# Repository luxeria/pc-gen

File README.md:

pc-gen
======

Signal generator using a pc audio output

The idea for this project is based on Debraj's pc based signal generator. 
(https://sites.google.com/site/hobbydebraj/home/pc-based-signal-generator)

The signal generator can be powered by a USB connection. 
Additionally the offset can be set up with the second output channel.

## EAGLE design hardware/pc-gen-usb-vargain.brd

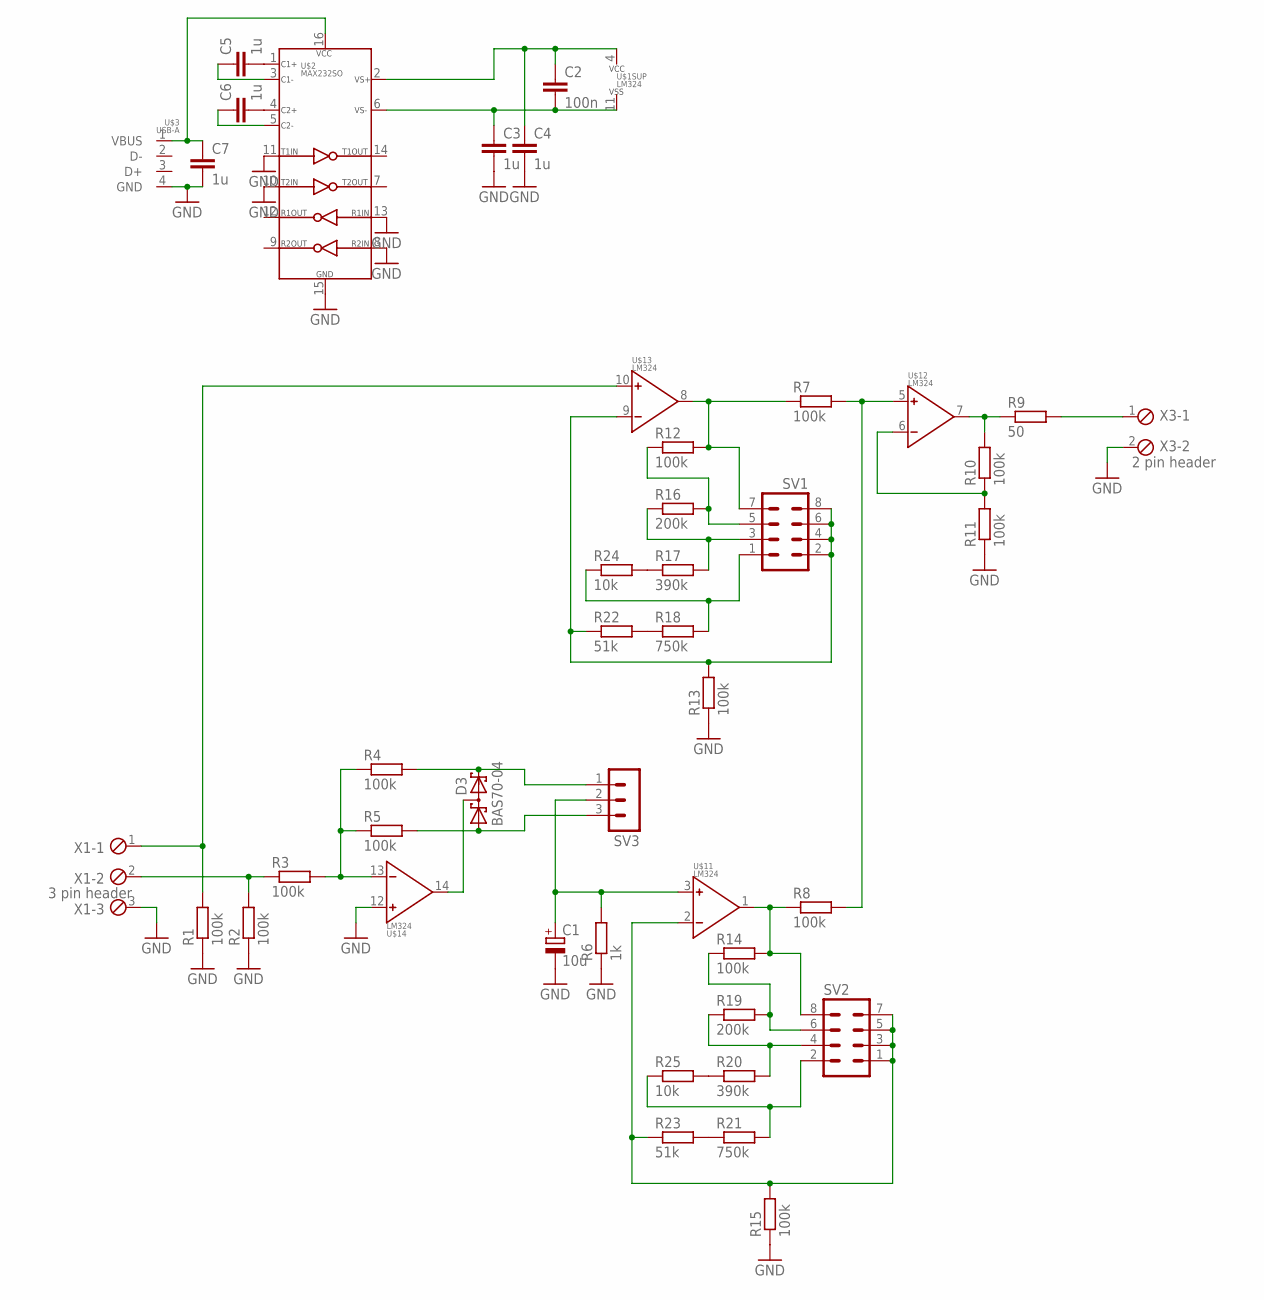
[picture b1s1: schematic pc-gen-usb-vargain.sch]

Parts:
C1: 10u; E2,5-7
C2: 100n; C1206
C3, C4, C5, C6, C7: 1u; C1206
D3: BAS70-04; SOT23
R1, R2, R3, R4, R5, R7, R8, R10, R11, R12, R13, R14, R15: 100k; R1206
R6: 1k; R1206
R9: 50; R1206
R16, R19: 200k; R1206
R17, R20: 390k; R1206
R18, R21: 750k; R1206
R22, R23: 51k; R1206
R24, R25: 10k; R1206
SV1, SV2: MA04-2
SV3: MA03-1
U$1: LM324; SO14
U$2: MAX232SO; SO16
U$3: USB-A
X1: 3 pin header; 3POL254
X3: 2 pin header; 2POL254

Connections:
GND: C1.-, C3.2, C4.2, C7.2, R1.1, R2.1, R6.1, R11.1, R13.1, R15.1, U$1.12 (POS), U$2.8 (R2IN), U$2.10 (T2IN), U$2.11 (T1IN), U$2.13 (R1IN), U$2.15 (GND), U$3.4 (GND), X1.3, X3.2
unnamed: C2.2, C3.1, U$1.11 (VSS), U$2.6 (VS-)
unnamed: C2.1, C4.1, U$1.4 (VCC), U$2.2 (VS+)
unnamed: R2.2, R3.1, X1.2
unnamed: R1.2, U$1.10 (POS), X1.1
unnamed: R16.1, R17.2, SV1.3
unnamed: R3.2, R4.1, R5.1, U$1.13 (NEG)
unnamed: D3.1 (A1), R5.2, SV3.3
unnamed: R7.1, R12.2, SV1.7, U$1.8 (OUT)
unnamed: D3.3 (C1A2), U$1.14 (OUT)
unnamed: R8.1, R14.2, SV2.8, U$1.1 (OUT)
unnamed: C1.+, R6.2, SV3.2, U$1.3 (POS)
unnamed: R18.2, R24.1, SV1.1
unnamed: R7.2, R8.2, U$1.5 (POS)
unnamed: R9.2, X3.1
unnamed: R9.1, R10.2, U$1.7 (OUT)
unnamed: R10.1, R11.2, U$1.6 (NEG)
unnamed: R12.1, R16.2, SV1.5
unnamed: C7.1, U$2.16 (VCC), U$3.1 (VBUS)
unnamed: C5.2, U$2.1 (C1+)
unnamed: C6.2, U$2.4 (C2+)
unnamed: C5.1, U$2.3 (C1-)
unnamed: C6.1, U$2.5 (C2-)
unnamed: R15.2, R23.1, SV2.1, SV2.3, SV2.5, SV2.7, U$1.2 (NEG)
unnamed: R19.1, R20.2, SV2.4
unnamed: R21.2, R25.1, SV2.2
unnamed: R14.1, R19.2, SV2.6
unnamed: R21.1, R23.2
unnamed: R20.1, R25.2
unnamed: R13.2, R22.1, SV1.2, SV1.4, SV1.6, SV1.8, U$1.9 (NEG)
unnamed: R18.1, R22.2
unnamed: R17.1, R24.2
unnamed: D3.2 (C2), R4.2, SV3.1

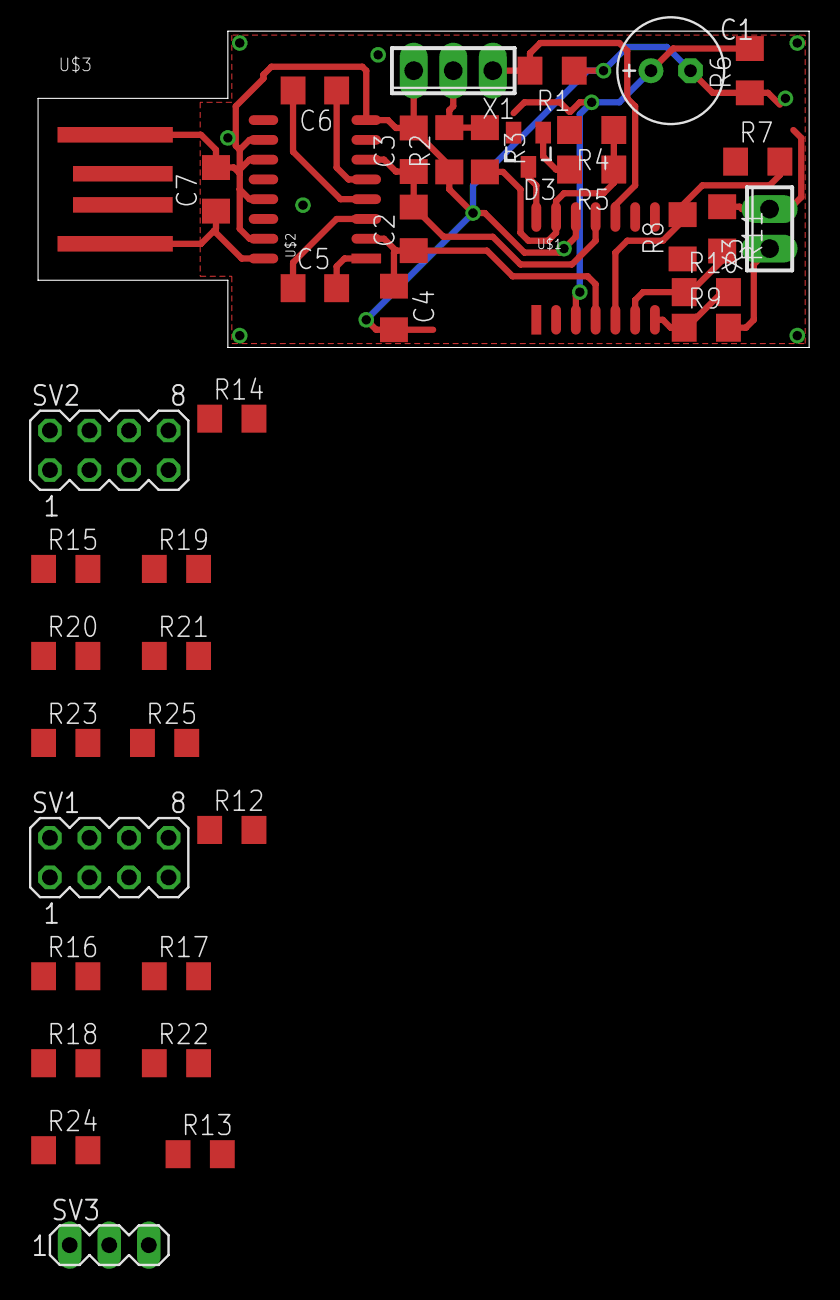
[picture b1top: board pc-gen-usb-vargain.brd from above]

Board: 2 copper layers, 49.5 x 20.3 mm, 41 parts (0 on the bottom side), 33 nets.

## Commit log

2013-11-12 Edit README, add reference to debraj's project.
2013-11-12 Folder structure created
2013-11-12 Initial version of schematic
2013-11-12 .gitignore
2013-11-20 .gitignore updated
2013-11-20 Prepared for Simulation
2013-11-24 Offset to input signal amplifier added
2013-11-24 Charge pump for symmetrical power supply
2013-11-25 USB connector on pcb
2013-11-26 Operational amplifier in DIL14
2013-11-27 Operational amplifier in SO14
2013-11-27 temporary eagle files added to .gitignore
2013-11-29 ideal rectifier improved
2013-12-01 simulation moved to folder sim
2013-12-02 >name and >value added
2013-12-03 MAX232
2013-12-03 temporary schematic and board files added to .gitignore
2013-12-04 Schematic for circuit on breadboard
2013-12-04 Layout for circuit on breadboard
2013-12-06 swaplevel of opamp changed to 1
2013-12-07 gain selector added
2013-12-07 offest polarity selector added
2013-12-08 small changes in layout to optimize pcb size
2013-12-09 small changes in layout
2013-12-09 generator with smd parts and pcb as usb connector
2013-12-09 schematic for smd version extended with variable gain and offset polarity
2014-04-23 Versuch mit gleichen Grenzfrequenzen
2014-04-24 High pass and Low pass with the same input signal
2014-04-24 high pass with oroginal signal and lowpass with modulated and rectified signal
2014-09-28 small changes
